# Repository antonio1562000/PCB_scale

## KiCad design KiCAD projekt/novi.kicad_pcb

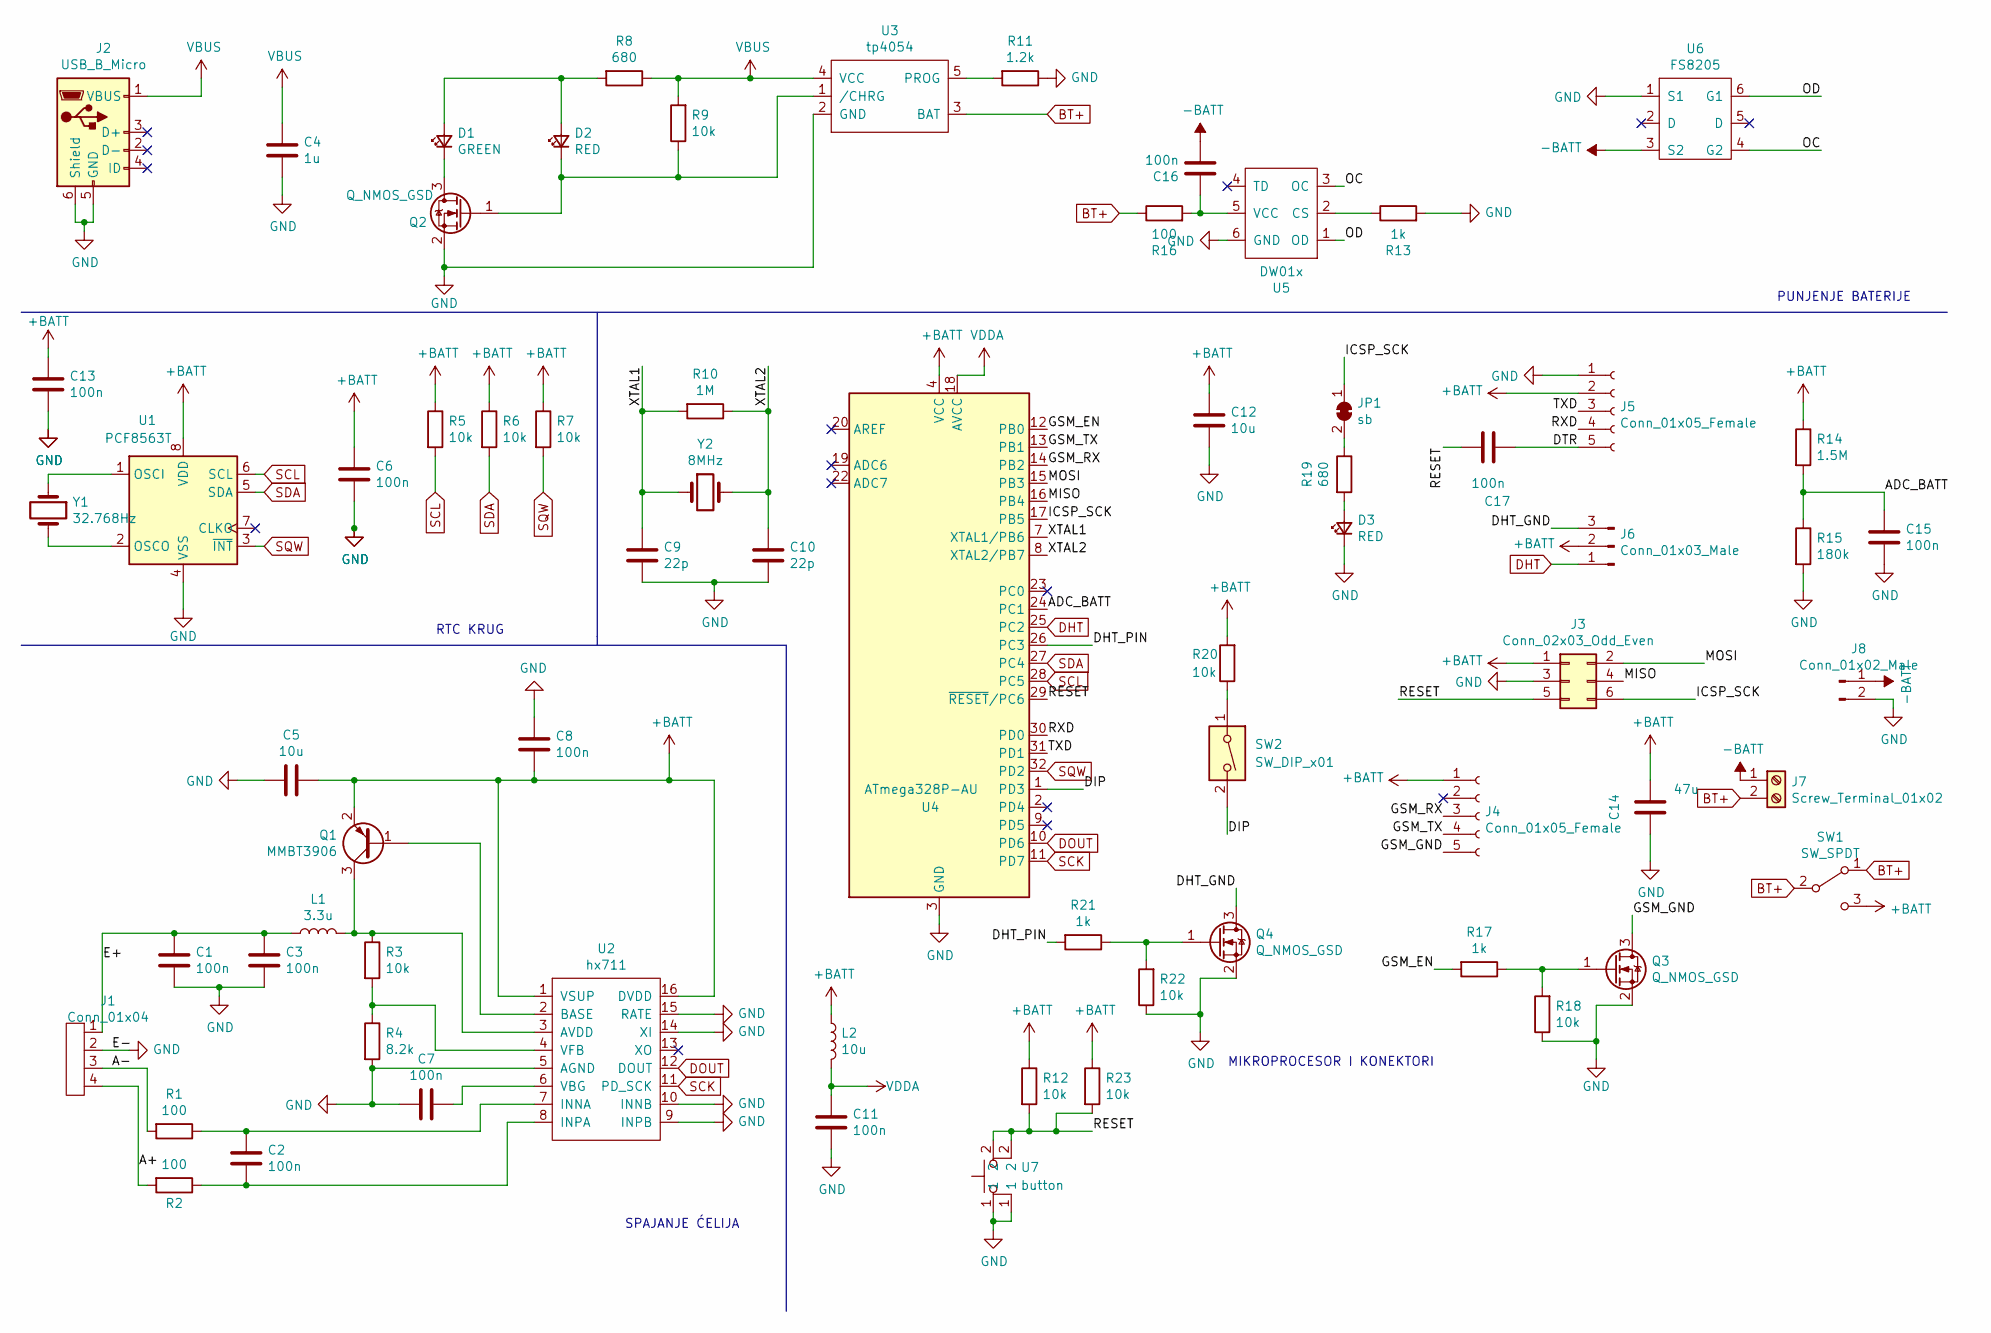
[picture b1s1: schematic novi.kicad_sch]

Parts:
C1, C2, C3, C6, C7, C8, C11, C13, C15, C16, C17: 100n; C_0402_1005Metric; LCSC C1525
C4: 1u; C_0603_1608Metric; LCSC C513775
C5, C12: 10u; C_0805_2012Metric; LCSC C15850
C9, C10: 22p; C_0402_1005Metric; LCSC C1555
C14: 47u; C_1206_3216Metric; LCSC C96123
D1: GREEN; LED_0603_1608Metric; LCSC C72043
D2, D3: RED; LED_0603_1608Metric; LCSC C2286
J1: Conn_01x04; hx711_conn; LCSC C918122
J2: USB_B_Micro; USB-Micro-B-Female-Jing-Extension-Electronic; LCSC C10418
J3: Conn_02x03_Odd_Even; PinHeader_2x03_P2.54mm_Vertical
J4: Conn_01x05_Female; PinSocket_1x05_P2.54mm_Vertical; LCSC C50950
J5: Conn_01x05_Female; PinHeader_1x05_P2.54mm_Vertical
J6: Conn_01x03_Male; TerminalBlock_Phoenix_MPT-0,5-3-2.54_1x03_P2.54mm_Horizontal; LCSC C474921
J7: Screw_Terminal_01x02; power_conn; LCSC C918120
J8: Conn_01x02_Male; PinHeader_1x02_P2.54mm_Vertical
JP1: sb; SolderJumper-2_P1.3mm_Bridged_Pad1.0x1.5mm
L1: 3.3u; L_0805_2012Metric; LCSC C51725
L2: 10u; L_0603_1608Metric; LCSC C1035
Q1: MMBT3906; SOT-23; LCSC C8326
Q2, Q3, Q4: Q_NMOS_GSD; SOT-23; LCSC C20917
R1, R2, R16: 100; R_0402_1005Metric; LCSC C25076
R3, R5, R6, R7, R9, R12, R18, R20, R22, R23: 10k; R_0402_1005Metric; LCSC C25744
R4: 8.2k; R_0603_1608Metric; LCSC C25981
R8, R19: 680; R_0603_1608Metric; LCSC C23228
R10: 1M; R_0603_1608Metric; LCSC C22935
R11: 1.2k; R_0603_1608Metric; LCSC C22765
R13, R17, R21: 1k; R_0603_1608Metric; LCSC C21190
R14: 1.5M; R_0603_1608Metric; LCSC C4172
R15: 180k; R_0603_1608Metric; LCSC C22827
SW1: SW_SPDT; switch; LCSC C5274459
SW2: SW_DIP_x01; SW_DIP_SPSTx01_Slide_9.78x4.72mm_W7.62mm_P2.54mm; LCSC C126888
U1: PCF8563T; SOIC-8_3.9x4.9mm_P1.27mm; LCSC C7440
U2: hx711; SOP-16_3.9x9.9mm_P1.27mm; LCSC C43656
U3: tp4054; SOT-23-5; LCSC C32574
U4: ATmega328P-AU; TQFP-32_7x7mm_P0.8mm; LCSC C14877
U5: DW01x; SOT-23-6; LCSC C14213
U6: FS8205; SOT-23-6; LCSC C2830320
U7: button; button1; LCSC C318884
Y1: 32.768Hz; Crystal_SMD_3215-2Pin_3.2x1.5mm; LCSC C32346
Y2: 8MHz; Crystal_SMD_5032-2Pin_5.0x3.2mm; LCSC C115962

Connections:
+BATT: C5.1, C6.1, C8.1, C12.1, C13.1, C14.1, J3.1, J4.1, J5.2, J6.2, L2.1, Q1.2 (E), R5.1, R6.1, R7.1, R12.1, R14.1, R20.2, R23.1, SW1.3 (C), U1.8 (VDD), U2.1 (VSUP), U2.16 (DVDD), U4.4 (VCC), U4.6 (VCC)
-BATT: C16.2, J7.1, J8.1, U6.3 (S2)
/A+: J1.4, R2.2
/A-: J1.3, R1.2
/ADC_BATT: C15.1, R14.2, R15.1, U4.24 (PC1)
/DHT_GND: J6.3, Q4.3 (D)
/DHT_PIN: R21.2, U4.26 (PC3)
/DIP: SW2.2, U4.1 (PD3)
/DTR: C17.2, J5.5
/E+: C1.1, C3.1, J1.1, L1.1
/GSM_EN: R17.2, U4.12 (PB0)
/GSM_GND: J4.5, Q3.3 (D)
/GSM_RX: J4.3, U4.14 (PB2)
/GSM_TX: J4.4, U4.13 (PB1)
/ICSP_SCK: J3.6, JP1.1 (A), U4.17 (PB5)
/MISO: J3.4, U4.16 (PB4)
/MOSI: J3.2, U4.15 (PB3)
/OC: U5.3 (OC), U6.4 (G2)
/OD: U5.1 (OD), U6.6 (G1)
/RESET: C17.1, J3.5, R12.2, R23.2, U4.29 (~RESET/PC6), U7.2
/RXD: J5.4, U4.30 (PD0)
/TXD: J5.3, U4.31 (PD1)
/XTAL1: C9.1, R10.2, U4.7 (XTAL1/PB6), Y2.1
/XTAL2: C10.1, R10.1, U4.8 (XTAL2/PB7), Y2.2
BT+: J7.2, R16.1, SW1.1 (A), SW1.2 (B), U3.3 (BAT)
DHT: J6.1, U4.25 (PC2)
DOUT: U2.12 (DOUT), U4.10 (PD6)
GND: C1.2, C3.2, C4.2, C5.2, C6.2, C7.2, C8.2, C9.2, C10.2, C11.2, C12.2, C13.2, C14.2, C15.2, D3.1 (K), J1.2, J2.5 (GND), J2.6 (Shield), J3.3, J5.1, J8.2, Q2.2 (S), Q3.2 (S), Q4.2 (S), R4.2, R11.1, R13.2, R15.2, R18.1, R22.1, U1.4 (VSS), U2.5 (AGND), U2.9 (INPB), U2.10 (INNB), U2.14 (XI), U2.15 (RATE), U3.2 (GND), U4.3 (GND), U4.5 (GND), U4.21 (GND), U5.6 (GND), U6.1 (S1), U7.1
unnamed: C2.1, R1.1, U2.7 (INNA)
unnamed: C2.2, R2.1, U2.8 (INPA)
unnamed: C7.1, U2.6 (VBG)
unnamed: C16.1, R16.2, U5.5 (VCC)
unnamed: D1.1 (K), Q2.3 (D)
unnamed: D1.2 (A), D2.2 (A), R8.2
unnamed: D2.1 (K), Q2.1 (G), R9.1, U3.1 (/CHRG)
unnamed: D3.2 (A), R19.2
unnamed: JP1.2 (B), R19.1
unnamed: L1.2, Q1.3 (C), R3.1, U2.3 (AVDD)
unnamed: Q1.1 (B), U2.2 (BASE)
unnamed: Q3.1 (G), R17.1, R18.2
unnamed: Q4.1 (G), R21.1, R22.2
unnamed: R3.2, R4.1, U2.4 (VFB)
unnamed: R11.2, U3.5 (PROG)
unnamed: R13.1, U5.2 (CS)
unnamed: R20.1, SW2.1
unnamed: U1.1 (OSCI), Y1.1
unnamed: U1.2 (OSCO), Y1.2
SCK: U2.11 (PD_SCK), U4.11 (PD7)
SCL: R5.2, U1.6 (SCL), U4.28 (PC5)
SDA: R6.2, U1.5 (SDA), U4.27 (PC4)
SQW: R7.2, U1.3 (~INT), U4.32 (PD2)
VBUS: C4.1, J2.1 (VBUS), R8.1, R9.2, U3.4 (VCC)
VDDA: C11.1, L2.2, U4.18 (AVCC)

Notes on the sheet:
SPAJANJE ĆELIJA
PUNJENJE BATERIJE
RTC KRUG
MIKROPROCESOR I KONEKTORI

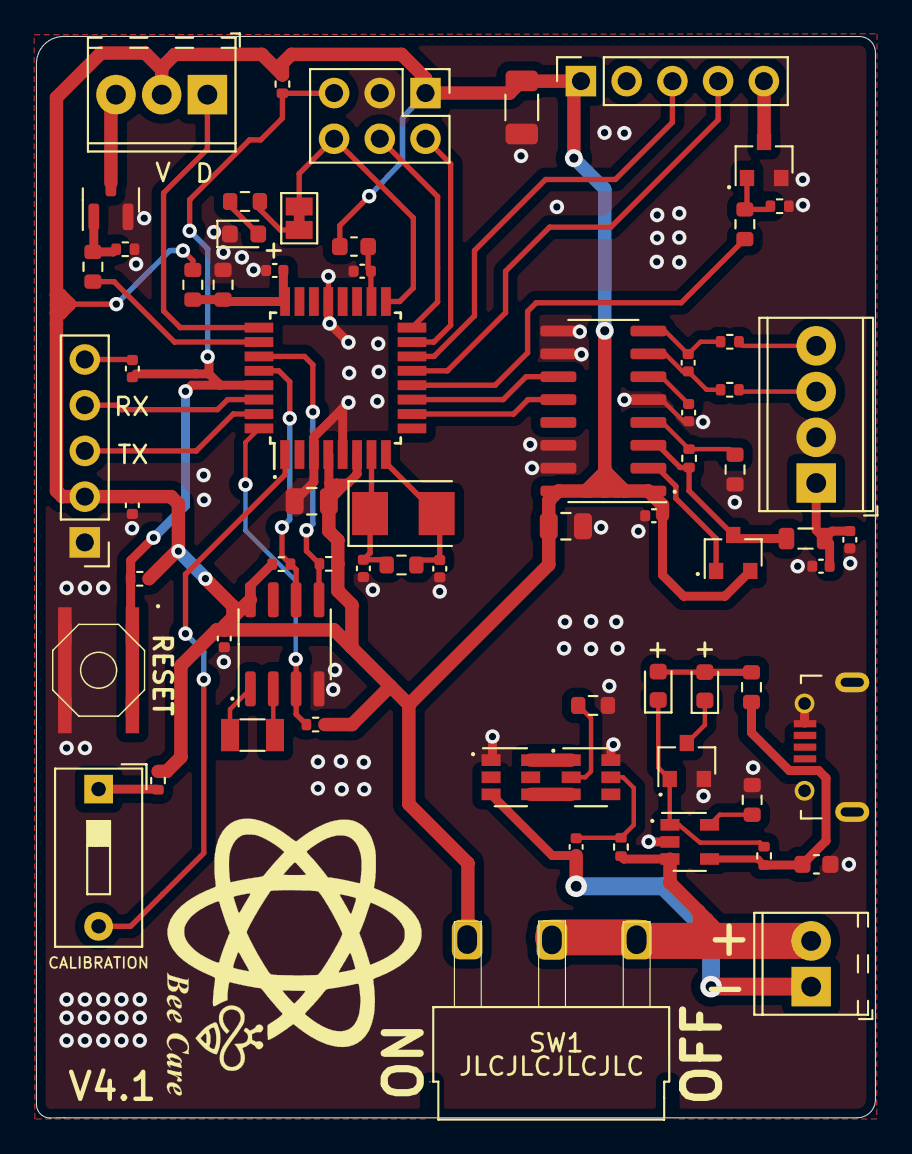
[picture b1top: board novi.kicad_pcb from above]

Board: 2 copper layers, 46.6 x 60.1 mm, 68 parts (0 on the bottom side), 53 nets.
